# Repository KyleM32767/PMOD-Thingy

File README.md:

# PMOD-Thingy

PMOD Thingy is, essentially, an Arduino Leonardo modified and repackaged to interface with basically any Digilent FPGA board via the PMOD headers. I designed it to streamline hardware security experiments done by myself and my colleagues at WPI Vernam Lab, where we'd use a 3.3V Arduino board to interface with an FPGA through the PMOD headers.

**Note: this is a custom board with a different pinout and clock frequency from a typical Arduino, so you must follow the setup procedure before use!**

## Pinouts

```
                  (top edge of board)
_______________________________________________________
-----------------------         -----------------------
| GND JB3 JB2 JB1 JB0 |         | GND JA3 JA2 JA1 JA0 |
| GND JB7 JB6 JB5 JB4 |         | GND JA7 JA6 JA5 JA4 |
-----------------------         -----------------------
```

| PMOD header | Digital I/O pin | Atmega32U4 pin |
|:------------|:----------------|:---------------|
| JA0         | 0               | PB0            |
| JA1         | 1 / SPI SCK     | PB1            |
| JA2         | 2 / SPI MOSI    | PB2            |
| JA3         | 3 / SPI MISO    | PB3            |
| JA4         | 4               | PB4            |
| JA5         | 5               | PB5            |
| JA6         | 6               | PB6            |
| JA7         | 7               | PB7            |
| JB0         | 8 / I2C SCL     | PD0            |
| JB1         | 9 / I2C SDA     | PD1            |
| JB2         | 10 / UART RX    | PD2            |
| JB3         | 11 / UART TX    | PD3            |
| JB4         | 12              | PD4            |
| JB5         | 13              | PD5            |
| JB6         | 14              | PD6            |
| JB7         | 15              | PD7            |

Although you can use the digital I/O numbers, there are macros for the PMOD headers, so you don't have to keep track of which header connects to which pin.

```cpp
// output 0 on JA6
pinMode(JA6, OUTPUT);
digitalWrite(JA6, LOW);

// input on JB2
pinMode(JB2, INPUT);
if (digitalRead(JB2) == HIGH)
	Serial.println("1 on JB2");
else
	Serial.println("0 on JB2");
```

Each PMOD header is also connected to a single port on the Atmega32U4, which means you can also read and write them bytewise using the data direction and port registers if that is more your speed. There are the macros `DDR_JA`/`DDR_JB` (data direction), `PIN_JA`/`PIN_JB` (input), and `PORT_JA`/`PORT_JB` (output) for that purpose. For more information, refer to [section 10.4 of the ATmega32U4 datasheet](https://ww1.microchip.com/downloads/en/devicedoc/atmel-7766-8-bit-avr-atmega16u4-32u4_datasheet.pdf#page=84). This makes reading and writing multiple bits much, much faster. The code snippet below is functionally identical to the one above...

```cpp
// output 0 on JA6
DDR_JA |= (1<<6);
PORT_JA &= ~(1<<6);

// read input on JB2
DDR_JB %= ~(1<<2);
if (PIN_JB & (1<<2))
	Serial.println("1 on JB2");
```

## Burning the bootloader

You can burn the bootloader to the PMOD thingy as you would any other Arduino board through the Arduino IDE. I prefer to do this with [another Arduino running ArduinoISP](https://docs.arduino.cc/built-in-examples/arduino-isp/ArduinoISP/) personally. It doesn't actually matter if you use a 3.3V or a 5V board, so long as you do not connect the PMOD Thingy to any other power source (i.e. USB) while using it. Just remember the capacitor between reset and ground!

**PLEASE NOTE: I MADE A MISTAKE!** If you have one of the original v1 boards I made, I mixed up the SPI pins, so a few of the ICSP pins (SCK, MOSI, MISO) are wrong, though VCC, GND, and RESET are correct. I corrected the labels for the SPI pins on the schematic in this repository and this readme, but not on the layout and gerber files, so if you make one of these yourself you will have this issue as well. In order to burn the bootloader from an Arduino Uno as ISP, you need to make the following connections...

| Pin   | Arduino Uno as ISP | PMOD Thingy V1 |
|:------|:-------------------|:---------------|
| MOSI  | D11 / ICSP-4       | JA2            |
| MISO  | D12 / ICSP-1       | JA3            |
| SCK   | D13 / ICSP-3       | JA1            |
| reset | D10                | ICSP-5         |

The PMOD Thingy runs the same bootloader as the Sparkfun Pro Micro 3.3V / 8MHz, though you can use the bootloader for any Atmega32u4-based Arduino with an 8MHz clock (as opposed to the 16MHz clock most boards run), if any other such boards exist at all. As such, you will need to [install the pro micro board to the Arduino IDE](https://learn.sparkfun.com/tutorials/pro-micro--fio-v3-hookup-guide#windows_boardaddon). Once that is installed, set up and connect your ArduinoISP, select "SparkFun Pro Micro" under *Tools>Board*, select "ATmega32U4 (3.3V, 8MHz)" under *Tools>Processor*, then click *Tools>Burn Bootloader*.

## Adding board to Arduino IDE

While you techincally *can* program the PMOD Thingy as a Sparkfun Pro Micro, it has an entirely different pinout from any standard Arduino. As such it needs its own special board definition. Use the following steps to add it...

1. **Open the Arduino AVR platform folder.** The exact location depends on your OS...
	* Windows
		- Arduino IDE 1.x - `C:\Program Files (x86)\Arduino\hardware\arduino\avr`
		- Arduino IDE 2.x - `C:\Users\{username}\AppData\Local\Arduino15\packages\arduino\hardware\avr\1.8.6`
	* macOS - `/Users/{username}/Library/Arduino15/packages/arduino/hardware/avr/1.8.6`
	* Linux - `/home/{username}/.arduino15/packages/arduino/hardware/avr/1.8.6`

2. **Modify `boards.txt`.** Paste the contents of `arduino_ide_config/boards_addon.txt` to the bottom of `boards.txt`

3. **Add a `pins_arduino.h` variant called 'pmodthingy.'** In the `variants` folder, create a folder called `pmodthingy` and paste `arduino_ide_config/pins_arduino.h`

4. **Restart Arduino IDE.** Once that is done, you should see "PMOD Thingy" as an option under *Tools>Board>Arduino AVR Boards*

## A few notes about Serial...

Since the PMOD Thingy has native USB you cannot use the serial port until it is actually open. In practice, this means you must put `while (!Serial) {}` or something after you initialize the serial interface and before you do anything with it. For more info, read the [official Arduino documentation](https://www.arduino.cc/reference/cs/language/functions/communication/serial/ifserial/)

**`SerialEvent()` does not work on Atmega32u4 based boards, such as the PMOD thingy.** However, completely undocumented is the ability to use it anyways with `SerialEventRun()`...

```cpp
// add this to your sketch make serialEvent() work
void SerialEventRun() {
	if (Serial.available())
		SerialEvent();
}
```

[People say using `serialEvent()` is the "wrong" thing to do](https://forum.arduino.cc/t/serialevent-with-the-esplora-leo-micro/173720), but it's what I've always done because I didn't know better at the time, and it works fine for what I usually do.

## "y no analog?"

The PMOD headers on FPGA boards, at least the ones I've used, are digital. Some boards have a PMOD header for XADC, but I've never used them and in fact have no idea how they work (as of writing this). As such, I've completely removed anything to do with analog inputs, though some of the pins are capable of analog and in fact are used as analog I/O on the Leonardo and Pro Micro.

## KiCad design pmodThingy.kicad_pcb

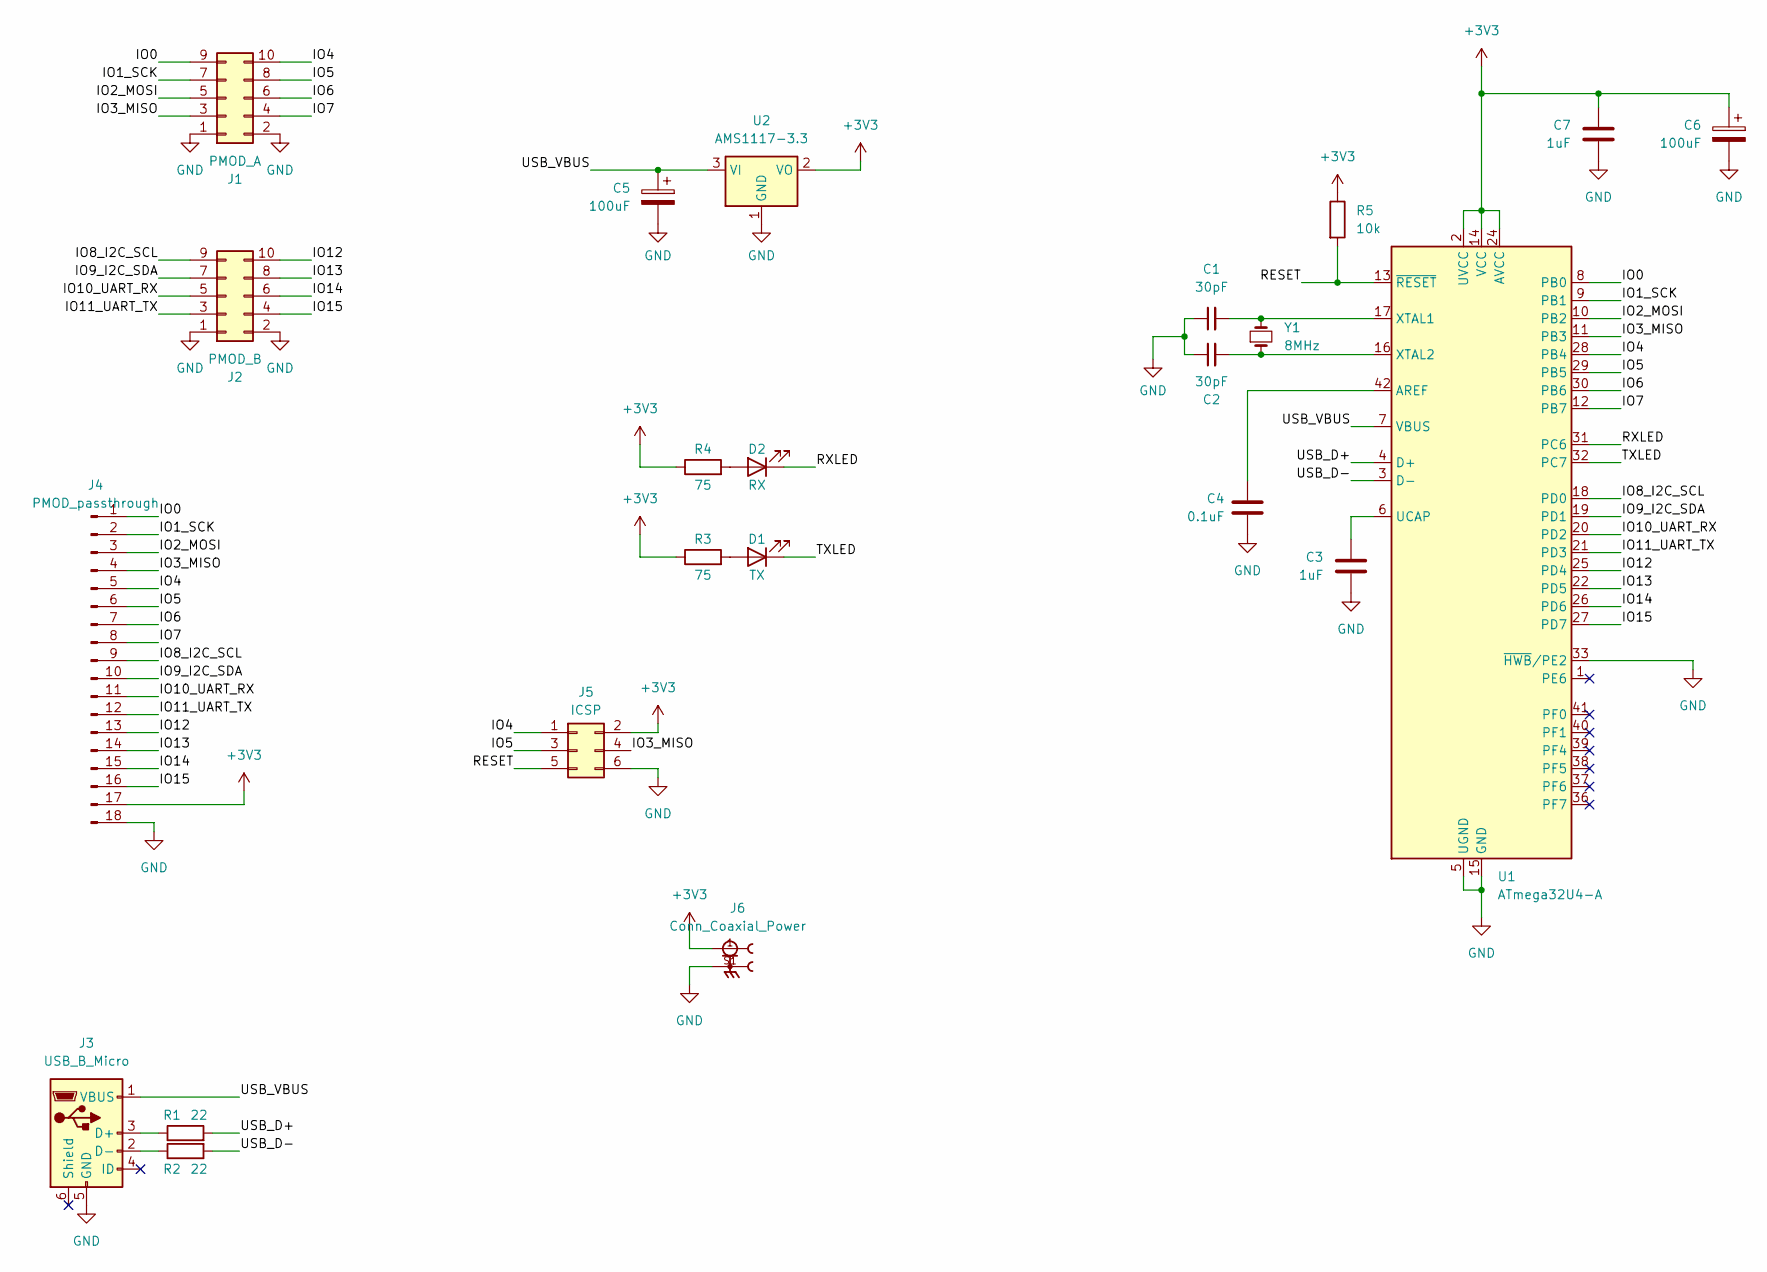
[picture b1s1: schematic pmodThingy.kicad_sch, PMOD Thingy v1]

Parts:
C1, C2: 30pF; C_0805_2012Metric_Pad1.18x1.45mm_HandSolder
C3, C7: 1uF; C_0805_2012Metric_Pad1.18x1.45mm_HandSolder
C4: 0.1uF; C_0805_2012Metric_Pad1.18x1.45mm_HandSolder
C5, C6: 100uF; CP_Elec_5x5.3
D1: TX; LED_0805_2012Metric_Pad1.15x1.40mm_HandSolder
D2: RX; LED_0805_2012Metric_Pad1.15x1.40mm_HandSolder
J1: PMOD_A; PinHeader_2x05_P2.54mm_Horizontal
J2: PMOD_B; PinHeader_2x05_P2.54mm_Horizontal
J3: USB_B_Micro; USB_Micro-B_GCT_USB3076-30-A
J4: PMOD_passthrough; PinHeader_1x18_P2.54mm_Horizontal
J5: ICSP; PinHeader_2x03_P2.54mm_Vertical
J6: Conn_Coaxial_Power; LINX_CONSMA001-C-G
R1, R2: 22; R_0805_2012Metric_Pad1.20x1.40mm_HandSolder
R3, R4: 75; R_0805_2012Metric_Pad1.20x1.40mm_HandSolder
R5: 10k; R_0805_2012Metric_Pad1.20x1.40mm_HandSolder
U1: ATmega32U4-A; TQFP-44_10x10mm_P0.8mm
U2: AMS1117-3.3; SOT-223-3_TabPin2
Y1: 8MHz; Crystal_SMD_HC49-SD_HandSoldering

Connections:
+3V3: C6.1, C7.1, J4.17, J5.2, J6.1, R3.1, R4.1, R5.1, U1.2 (UVCC), U1.14 (VCC), U1.24 (AVCC), U1.34 (VCC), U1.44 (AVCC), U2.2 (VO)
/IO0: J1.9, J4.1, U1.8 (PB0)
/IO1_SCK: J1.7, J4.2, U1.9 (PB1)
/IO2_MOSI: J1.5, J4.3, U1.10 (PB2)
/IO3_MISO: J1.3, J4.4, J5.4, U1.11 (PB3)
/IO4: J1.10, J4.5, J5.1, U1.28 (PB4)
/IO5: J1.8, J4.6, J5.3, U1.29 (PB5)
/IO6: J1.6, J4.7, U1.30 (PB6)
/IO7: J1.4, J4.8, U1.12 (PB7)
/IO8_I2C_SCL: J2.9, J4.9, U1.18 (PD0)
/IO9_I2C_SDA: J2.7, J4.10, U1.19 (PD1)
/IO10_UART_RX: J2.5, J4.11, U1.20 (PD2)
/IO11_UART_TX: J2.3, J4.12, U1.21 (PD3)
/IO12: J2.10, J4.13, U1.25 (PD4)
/IO13: J2.8, J4.14, U1.22 (PD5)
/IO14: J2.6, J4.15, U1.26 (PD6)
/IO15: J2.4, J4.16, U1.27 (PD7)
/RESET: J5.5, R5.2, U1.13 (~RESET)
/RXLED: D2.1 (K), U1.31 (PC6)
/TXLED: D1.1 (K), U1.32 (PC7)
/USB_D+: R1.2, U1.4 (D+)
/USB_D-: R2.2, U1.3 (D-)
/USB_VBUS: C5.1, J3.1 (VBUS), U1.7 (VBUS), U2.3 (VI)
GND: C1.1, C2.1, C3.2, C4.2, C5.2, C6.2, C7.2, J1.1, J1.2, J2.1, J2.2, J3.5 (GND), J4.18, J5.6, J6.S1, U1.5 (UGND), U1.15 (GND), U1.23 (GND), U1.33 (~HWB/PE2), U1.35 (GND), U1.43 (GND), U2.1 (GND)
unnamed: D1.2 (A), R3.2
unnamed: D2.2 (A), R4.2
unnamed: J3.3 (D+), R1.1
unnamed: J3.2 (D-), R2.1
unnamed: C4.1, U1.42 (AREF)
unnamed: C3.1, U1.6 (UCAP)
unnamed: C1.2, U1.17 (XTAL1), Y1.2
unnamed: C2.2, U1.16 (XTAL2), Y1.1

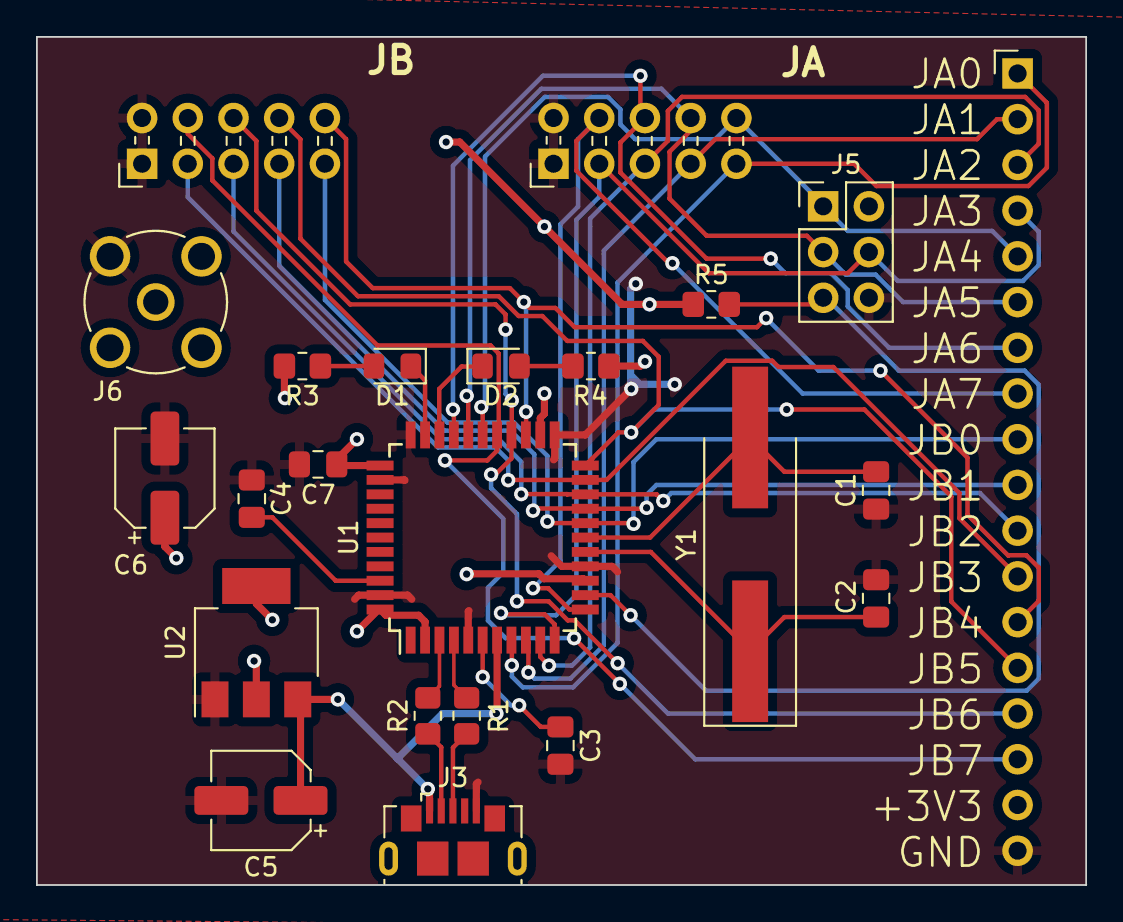
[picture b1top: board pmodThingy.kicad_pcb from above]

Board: 2 copper layers, 58.3 x 47.1 mm, 23 parts (0 on the bottom side), 32 nets.

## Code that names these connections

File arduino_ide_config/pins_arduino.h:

/*
  pins_arduino.h - Pin definition functions for Arduino
  Part of Arduino - http://www.arduino.cc/

  Copyright (c) 2007 David A. Mellis

  This library is free software; you can redistribute it and/or
  modify it under the terms of the GNU Lesser General Public
  License as published by the Free Software Foundation; either
  version 2.1 of the License, or (at your option) any later version.

  This library is distributed in the hope that it will be useful,
  but WITHOUT ANY WARRANTY; without even the implied warranty of
  MERCHANTABILITY or FITNESS FOR A PARTICULAR PURPOSE.  See the GNU
  Lesser General Public License for more details.

  You should have received a copy of the GNU Lesser General
  Public License along with this library; if not, write to the
  Free Software Foundation, Inc., 59 Temple Place, Suite 330,
  Boston, MA  02111-1307  USA
*/

#ifndef Pins_Arduino_h
#define Pins_Arduino_h

#include <avr/pgmspace.h>

// Workaround for wrong definitions in "iom32u4.h".
// This should be fixed in the AVR toolchain.
#undef UHCON
#undef UHINT
#undef UHIEN
#undef UHADDR
#undef UHFNUM
#undef UHFNUML
#undef UHFNUMH
#undef UHFLEN
#undef UPINRQX
#undef UPINTX
#undef UPNUM
#undef UPRST
#undef UPCONX
#undef UPCFG0X
#undef UPCFG1X
#undef UPSTAX
#undef UPCFG2X
#undef UPIENX
#undef UPDATX
#undef TCCR2A
#undef WGM20
#undef WGM21
#undef COM2B0
#undef COM2B1
#undef COM2A0
#undef COM2A1
#undef TCCR2B
#undef CS20
#undef CS21
#undef CS22
#undef WGM22
#undef FOC2B
#undef FOC2A
#undef TCNT2
#undef TCNT2_0
#undef TCNT2_1
#undef TCNT2_2
#undef TCNT2_3
#undef TCNT2_4
#undef TCNT2_5
#undef TCNT2_6
#undef TCNT2_7
#undef OCR2A
#undef OCR2_0
#undef OCR2_1
#undef OCR2_2
#undef OCR2_3
#undef OCR2_4
#undef OCR2_5
#undef OCR2_6
#undef OCR2_7
#undef OCR2B
#undef OCR2_0
#undef OCR2_1
#undef OCR2_2
#undef OCR2_3
#undef OCR2_4
#undef OCR2_5
#undef OCR2_6
#undef OCR2_7

#define NUM_DIGITAL_PINS  18
#define NUM_ANALOG_INPUTS 0

#define TX_RX_LED_INIT	DDRC |= (1<<6), DDRC |= (1<<7)
#define TXLED0			PORTC |= (1<<7)
#define TXLED1			PORTC &= ~(1<<7)
#define RXLED0			PORTC |= (1<<6)
#define RXLED1			PORTC &= ~(1<<6)

#define PIN_WIRE_SDA         (8)
#define PIN_WIRE_SCL         (9)

// port and data direction registers for byte-wise writing PMOD headers
#define DDR_JA  DDRB
#define PORT_JA PORTB
#define PIN_JA  PINB
#define DDR_JB  DDRD
#define PORT_JB PORTD
#define PIN_JB  PIND

// macros for each pin
#define JA0 0
#define JA1 1
#define JA2 2
#define JA3 3
#define JA4 4
#define JA5 5
#define JA6 6
#define JA7 7
#define JB0 8
#define JB1 9
#define JB2 10
#define JB3 11
#define JB4 12
#define JB5 13
#define JB6 14
#define JB7 15


static const uint8_t SDA = PIN_WIRE_SDA;
static const uint8_t SCL = PIN_WIRE_SCL;

// #define LED_BUILTIN 12
#define LED_BUILTIN_RX 16
#define LED_BUILTIN_TX 17

// Map SPI port to 'new' pins D14..D17
#define PIN_SPI_SS    (0)
#define PIN_SPI_MOSI  (2)
#define PIN_SPI_MISO  (3)
#define PIN_SPI_SCK   (1)

static const uint8_t SS   = PIN_SPI_SS;
static const uint8_t MOSI = PIN_SPI_MOSI;
static const uint8_t MISO = PIN_SPI_MISO;
static const uint8_t SCK  = PIN_SPI_SCK;

#define digitalPinToPCICR(p)    ( ((p) >= 0 && (p) <= 7) ? (&PCICR) : ((uint8_t *)0))
#define digitalPinToPCICRbit(p) 0
#define digitalPinToPCMSK(p)    (((p) >= 0 && (p) <= 7) ? (&PCMSK0) : ((uint8_t *)0))
#define digitalPinToPCMSKbit(p) (p)

//	__AVR_ATmega32U4__ has an unusual mapping of pins to channels
extern const uint8_t PROGMEM analog_pin_to_channel_PGM[];
#define analogPinToChannel(P)  ( pgm_read_byte( analog_pin_to_channel_PGM + (P) ) )

#define digitalPinHasPWM(p)         ((p) == 8 || (p) == 15 || (p) == 5 || (p) == 6 || (p) == 7)

#define digitalPinToInterrupt(p) ((p) == 10 ? 2 : ((p) == 11 ? 3 : ((p) == 9 ? 1 : ((p) == 8 ? 0 : NOT_AN_INTERRUPT))))

#ifdef ARDUINO_MAIN

// On the Arduino board, digital pins are also used
// for the analog output (software PWM).  Analog input
// pins are a separate set.

// ATMEL ATMEGA32U4 / ARDUINO LEONARDO
//
// D0				PD2					RXD1/INT2
// D1				PD3					TXD1/INT3
// D2				PD1		SDA			SDA/INT1
// D3#				PD0		PWM8/SCL	OC0B/SCL/INT0
// D4		A6		PD4					ADC8
// D5#				PC6		???			OC3A/#OC4A
// D6#		A7		PD7		FastPWM		#OC4D/ADC10
// D7				PE6					INT6/AIN0
//
// D8		A8		PB4					ADC11/PCINT4
// D9#		A9		PB5		PWM16		OC1A/#OC4B/ADC12/PCINT5
// D10#		A10		PB6		PWM16		OC1B/0c4B/ADC13/PCINT6
// D11#				PB7		PWM8/16		0C0A/OC1C/#RTS/PCINT7
// D12		A11		PD6					T1/#OC4D/ADC9
// D13#				PC7		PWM10		CLK0/OC4A
//
// A0		D18		PF7					ADC7
// A1		D19		PF6					ADC6
// A2		D20 	PF5					ADC5
// A3		D21 	PF4					ADC4
// A4		D22		PF1					ADC1
// A5		D23 	PF0					ADC0
//
// New pins D14..D17 to map SPI port to digital pins
//
// MISO		D14		PB3					MISO,PCINT3
// SCK		D15		PB1					SCK,PCINT1
// MOSI		D16		PB2					MOSI,PCINT2
// SS		D17		PB0					RXLED,SS/PCINT0
//
// TXLED	D30		PD5					XCK1
// RXLED	D17	    PB0
// HWB				PE2					HWB

// these arrays map port names (e.g. port B) to the
// appropriate addresses for various functions (e.g. reading
// and writing)
const uint16_t PROGMEM port_to_mode_PGM[] = {
	NOT_A_PORT,
	NOT_A_PORT,
	(uint16_t) &DDRB,
	(uint16_t) &DDRC,
	(uint16_t) &DDRD,
	(uint16_t) &DDRE,
	(uint16_t) &DDRF,
};

const uint16_t PROGMEM port_to_output_PGM[] = {
	NOT_A_PORT,
	NOT_A_PORT,
	(uint16_t) &PORTB,
	(uint16_t) &PORTC,
	(uint16_t) &PORTD,
	(uint16_t) &PORTE,
	(uint16_t) &PORTF,
};

const uint16_t PROGMEM port_to_input_PGM[] = {
	NOT_A_PORT,
	NOT_A_PORT,
	(uint16_t) &PINB,
	(uint16_t) &PINC,
	(uint16_t) &PIND,
	(uint16_t) &PINE,
	(uint16_t) &PINF,
};

const uint8_t PROGMEM digital_pin_to_port_PGM[] = {

	// PMOD JA - port B
	PB, // D0  - JA0 - PB0
	PB,	// D1  - JA1 - PB1
	PB, // D2  - JA2 - P2B
	PB,	// D3  - JA3 - PB3
	PB,	// D4  - JA4 - PB4
	PB, // D5  - JA5 - PB5
	PB, // D6  - JA6 - PB6
	PB, // D7  - JA7 - PB7
	
	// PMOD JB - port D
	PD, // D8  - JB0 - PD0
	PD,	// D9  - JB1 - PD1
	PD, // D10 - JB2 - PD2
	PD,	// D11 - JB3 - PD3
	PD, // D12 - JB4 - PD4
	PD, // D13 - JB5 - PD5
	PD,	// D14 - JB6 - PD6
	PD,	// D15 - JB7 - PD7

	PC,
	PC,
};

const uint8_t PROGMEM digital_pin_to_bit_mask_PGM[] = {
	
	// PMOD JA - port B
	_BV(0), // D0  - JA0 - PB0
	_BV(1), // D1  - JA1 - P1B
	_BV(2), // D2  - JA2 - P2B
	_BV(3), // D3  - JA3 - PB3
	_BV(4), // D4  - JA4 - PB4
	_BV(5), // D5  - JA5 - PB5
	_BV(6), // D6  - JA6 - PB6
	_BV(7), // D7  - JA7 - PB7

	// PMOD JB - port D
	_BV(0), // D8  - JB0 - PD0
	_BV(1), // D9  - JB1 - P1D
	_BV(2), // D10 - JB2 - P2D
	_BV(3), // D11 - JB3 - PD3
	_BV(4), // D12 - JB4 - PD4
	_BV(5), // D13 - JB5 - PD5
	_BV(6), // D14 - JB6 - PD6
	_BV(7), // D15 - JB7 - PD7

	_BV(6), // D16 - RXLED - PC6
	_BV(7), // D17 - TXLED - PC7
};

const uint8_t PROGMEM digital_pin_to_timer_PGM[] = {
	NOT_ON_TIMER,	
	NOT_ON_TIMER,
	NOT_ON_TIMER,
	NOT_ON_TIMER,
	NOT_ON_TIMER,	
	TIMER1A,		/* JA5 */
	TIMER1B,		/* JA6 */
	TIMER0A,		/* JB7 */
	
	TIMER0B,		/* JB0 */
	NOT_ON_TIMER,
	NOT_ON_TIMER,	
	NOT_ON_TIMER,
	NOT_ON_TIMER,
	NOT_ON_TIMER,	
	NOT_ON_TIMER,	
	TIMER4D,		/* JB7 */

	NOT_ON_TIMER,
	NOT_ON_TIMER,
};

const uint8_t PROGMEM analog_pin_to_channel_PGM[] = {};

#endif /* ARDUINO_MAIN */

// These serial port names are intended to allow libraries and architecture-neutral
// sketches to automatically default to the correct port name for a particular type
// of use.  For example, a GPS module would normally connect to SERIAL_PORT_HARDWARE_OPEN,
// the first hardware serial port whose RX/TX pins are not dedicated to another use.
//
// SERIAL_PORT_MONITOR        Port which normally prints to the Arduino Serial Monitor
//
// SERIAL_PORT_USBVIRTUAL     Port which is USB virtual serial
//
// SERIAL_PORT_LINUXBRIDGE    Port which connects to a Linux system via Bridge library
//
// SERIAL_PORT_HARDWARE       Hardware serial port, physical RX & TX pins.
//
// SERIAL_PORT_HARDWARE_OPEN  Hardware serial ports which are open for use.  Their RX & TX
//                            pins are NOT connected to anything by default.
#define SERIAL_PORT_MONITOR        Serial
#define SERIAL_PORT_USBVIRTUAL     Serial
#define SERIAL_PORT_HARDWARE       Serial1
#define SERIAL_PORT_HARDWARE_OPEN  Serial1

// Alias SerialUSB to Serial
#define SerialUSB SERIAL_PORT_USBVIRTUAL

#endif /* Pins_Arduino_h */

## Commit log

2024-12-17 add v1 KiCad files
2024-12-17 add arduino IDE config files
2024-12-17 relabel some pins on schematic
2025-04-25 added missing macro for JA and JB inputs
